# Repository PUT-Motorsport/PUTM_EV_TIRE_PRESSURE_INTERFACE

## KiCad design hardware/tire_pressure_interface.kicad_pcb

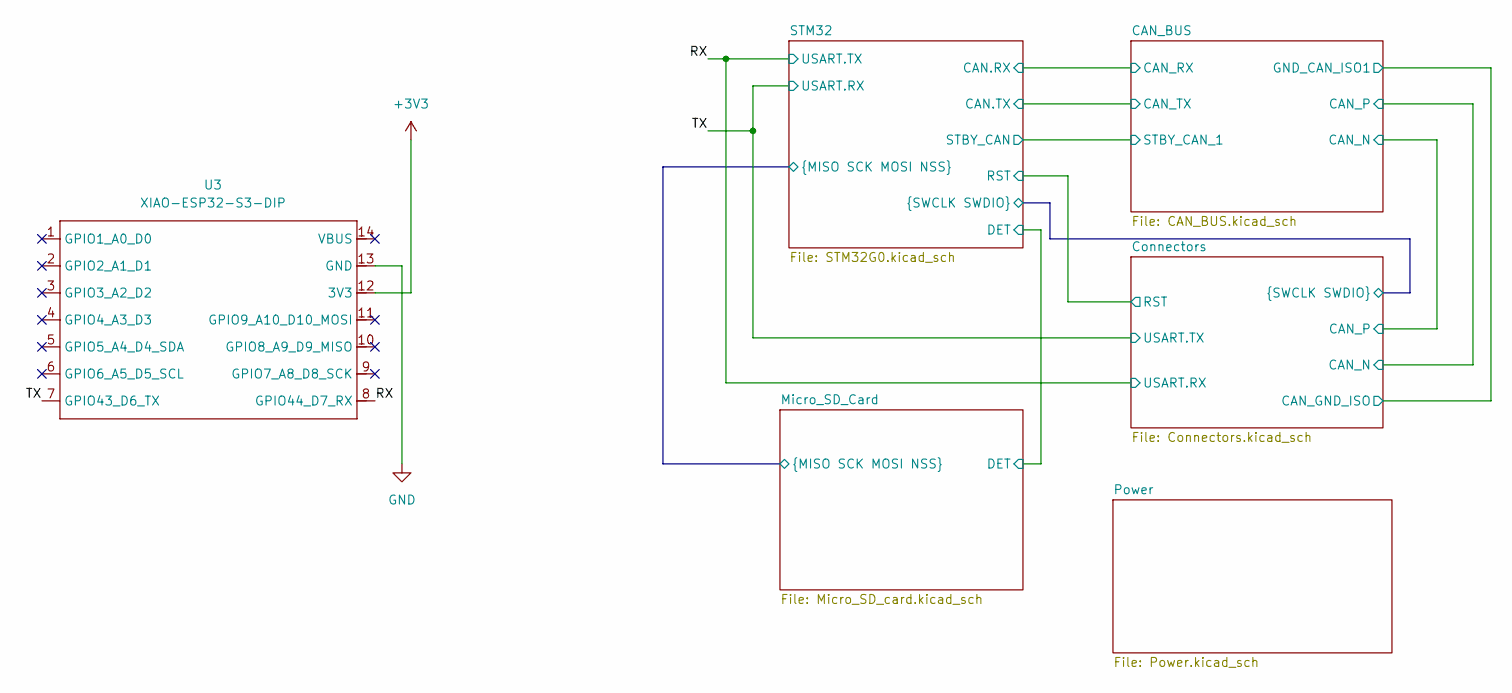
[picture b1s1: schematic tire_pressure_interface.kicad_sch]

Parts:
U3: XIAO-ESP32-S3-DIP

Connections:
+3V3: U3.12 (3V3); also elsewhere on the board
/RX: U3.8 (GPIO44_D7_RX); also elsewhere on the board
/TX: U3.7 (GPIO43_D6_TX); also elsewhere on the board
GND: U3.13 (GND); also elsewhere on the board

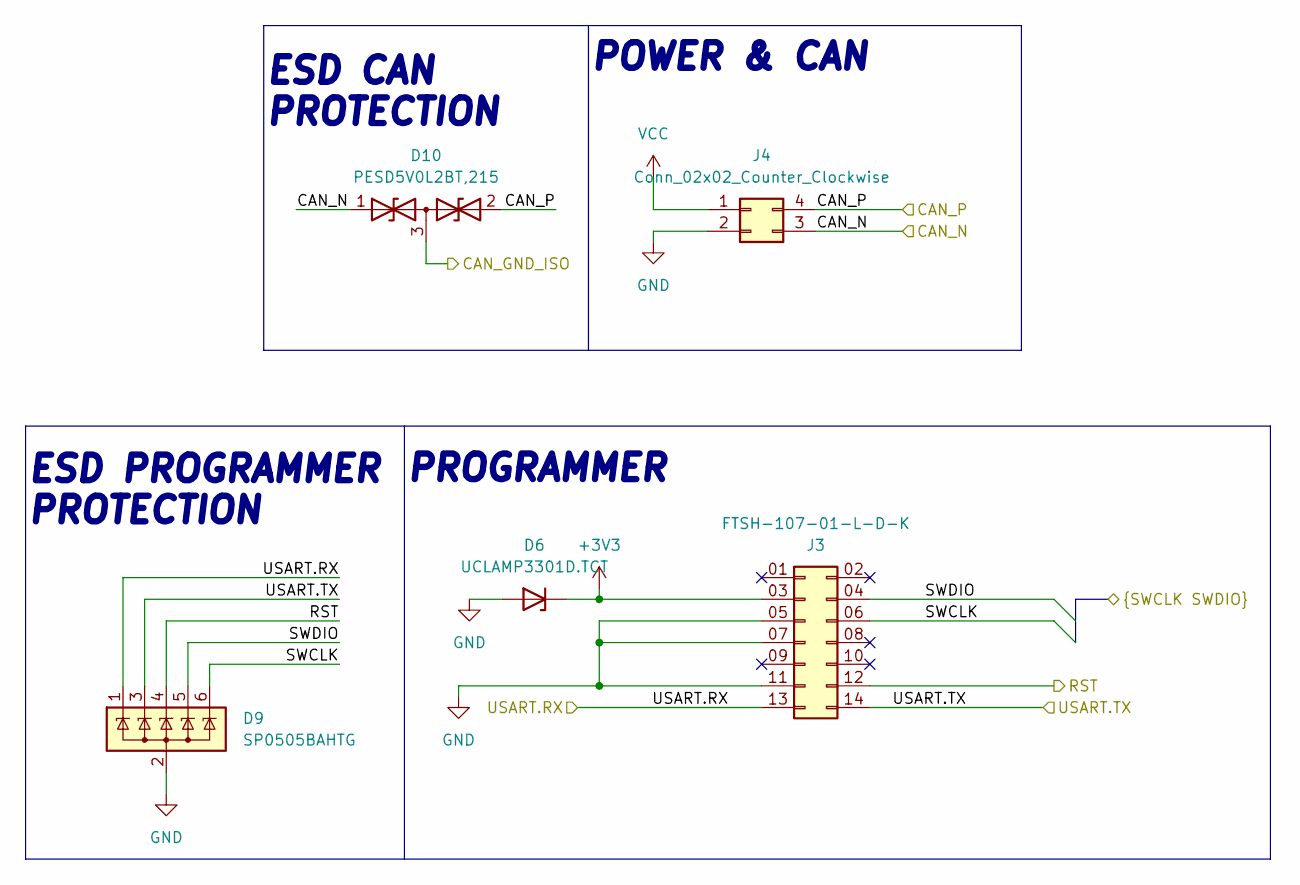
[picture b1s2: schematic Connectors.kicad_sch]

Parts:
D6: UCLAMP3301D.TCT; D_SOD-323_HandSoldering; Mouser number 947-UCLAMP3301D.TCT
D9: SP0505BAHTG; SOT-23-6_Handsoldering; Mouser Part Number 576-SP0505BAHTG
D10: PESD5V0L2BT,215; SOT-23-3; Mouser Part Number 771-PESD5V0S2BT-QR
J3: FTSH-107-01-L-D-K; SAMTEC_FTSH-107-01-L-D-K; Mouser Part Number 200-FTSH10701LDK
J4: Conn_02x02_Counter_Clockwise; JST_EH_S4B-EH_1x04_P2.50mm_Horizontal; Mouser part number 306-S4B-EHLFSN

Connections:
+3V3: D6.1 (K), J3.03 (Pin_3); also elsewhere on the board
/CAN_BUS/GND_CAN_ISO1: D10.3 (common); also elsewhere on the board
/Connectors/CAN_N: D10.1 (A1), J4.3; also elsewhere on the board
/Connectors/CAN_P: D10.2 (A2), J4.4; also elsewhere on the board
/Connectors/RST: D9.4 (K), J3.12; also elsewhere on the board
/Connectors/SWCLK: D9.6 (K), J3.06 (Pin_6); also elsewhere on the board
/Connectors/SWDIO: D9.5 (K), J3.04 (Pin_4); also elsewhere on the board
/RX: D9.1 (K), J3.13; also elsewhere on the board
/TX: D9.3 (K), J3.14; also elsewhere on the board
GND: D6.2 (A), D9.2 (A), J3.05 (Pin_5), J3.07 (Pin_7), J3.11, J4.2; also elsewhere on the board
VCC: J4.1; also elsewhere on the board

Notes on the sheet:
ESD PROGRAMMER PROTECTION
PROGRAMMER
POWER & CAN
ESD CAN PROTECTION

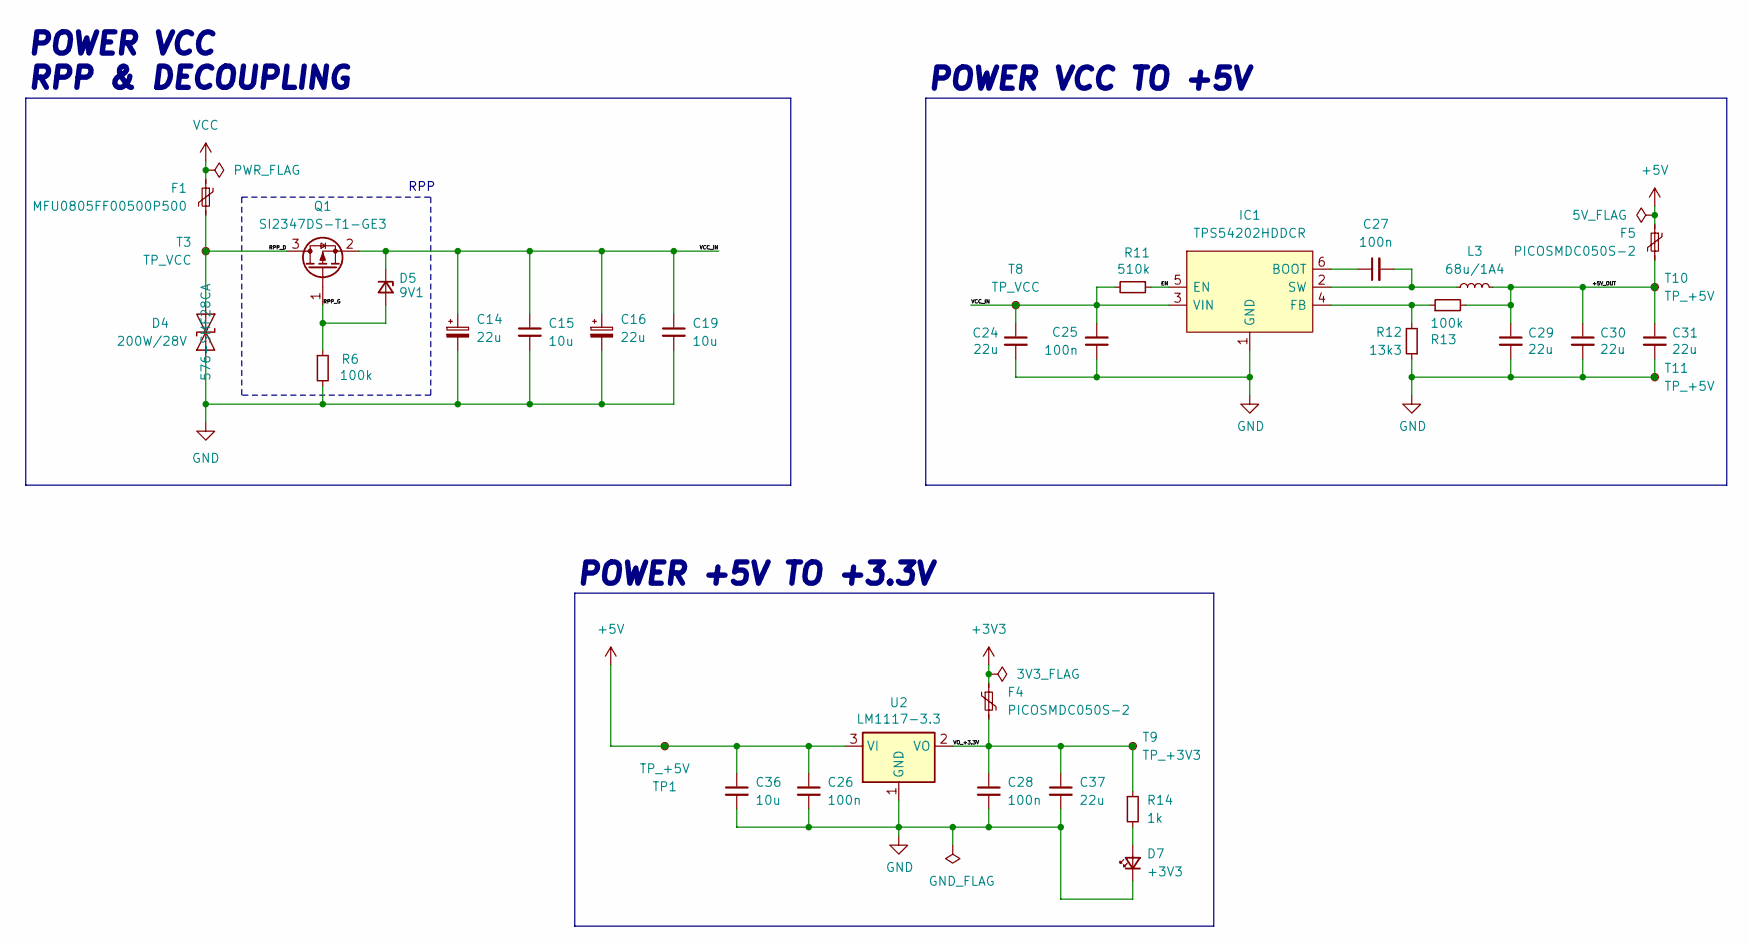
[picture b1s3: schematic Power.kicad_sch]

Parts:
C14, C16: 22u; CP_Elec_4x5.8; Mouser part number 647-UCM1V220MCL1GS
C15, C19: 10u; C_0805_2012Metric_Pad1.18x1.45mm_HandSolder; Mouser part number 810-C2012X5R1V106M0C
C24, C29, C30, C31: 22u; C_0805_2012Metric_Pad1.18x1.45mm_HandSolder; Manufacturer_Part_Number CL21A107MQYNNWE; Mouser Part Number 81-ZRA21CR61E226ME1L
C25, C27: 100n; C_0603_1608Metric_Pad1.08x0.95mm_HandSolder; Manufacturer_Part_Number MAJCU168BB7104KTEA01; Mouser Part Number 963-MAJCU168BB7104KT
C26, C28: 100n; C_0603_1608Metric_Pad1.08x0.95mm_HandSolder; Mouser part number 963-MAJCU168BB7104KT
C36: 10u; C_0603_1608Metric_Pad1.08x0.95mm_HandSolder; Mouser part number 187-CL10A106MA8NRWC
C37: 22u; C_0805_2012Metric_Pad1.18x1.45mm_HandSolder; Mouser part number 81-ZRA21CR61E226ME1L
D4: 200W/28V; D_SOD-123; Mouser part number 576-SMF28CA
D5: 9V1; D_SOD-323_HandSoldering; Mouser part number 863-SZMM3Z9V1T1G
D7: +3V3; LED_0603_1608Metric_Pad1.05x0.95mm_HandSolder
F1: MFU0805FF00500P500; Fuse_0805_2012Metric_Pad1.15x1.40mm_HandSolder; Mouser part number 594-MFU0805FF00500P1
F4, F5: PICOSMDC050S-2; Fuse_0805_2012Metric_Pad1.15x1.40mm_HandSolder
IC1: TPS54202HDDCR; SOT-23-6_Handsoldering; Mouser Part Number 595-TPS54202HDDCR
L3: 68u/1A4; L_TDK_VLS6045EX_VLS6045AF; Mouser Part Number 810-VLS6045EX-680M
Q1: SI2347DS-T1-GE3; SOT-23-3; Mouser part number 78-SI2347DS-T1-GE3
R6: 100k; R_0603_1608Metric_Pad0.98x0.95mm_HandSolder; Mouser part number 660-RK73B1JTTD104J
R11: 510k; R_0603_1608Metric_Pad0.98x0.95mm_HandSolder; Manufacturer_Part_Number RT0603DRD07510KL; Mouser Part Number 603-RT0603DRD07510KL
R12: 13k3; R_0603_1608Metric_Pad0.98x0.95mm_HandSolder; Manufacturer_Part_Number RT0603DRE0713K3L; Mouser Part Number 603-RT0603DRE0713K3L
R13: 100k; R_0603_1608Metric_Pad0.98x0.95mm_HandSolder; Manufacturer_Part_Number RT0603DRE07100KL; Mouser Part Number 603-RT0603DRE07100KL
R14: 1k; R_0603_1608Metric_Pad0.98x0.95mm_HandSolder
T3, T8: TP_VCC; TestPoint_Pad_1.0x1.0mm
T9: TP_+3V3; TestPoint_Pad_1.0x1.0mm
T10, T11: TP_+5V; TestPoint_Pad_1.0x1.0mm
TP1: TP_+5V; TestPoint_Pad_1.0x1.0mm
U2: LM1117-3.3; SOT-223-3_TabPin2

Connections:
+3V3: F4.1; also elsewhere on the board
+5V: C26.1, C36.1, F5.1, TP1.1 (1_1), U2.3 (VI); also elsewhere on the board
/Power/+5V_OUT: C29.1, C30.1, C31.1, F5.2, L3.2, R13.2, T10.1 (1_1)
/Power/EN: IC1.5 (EN), R11.1
/Power/RPP_D: D4.2 (A2), F1.2, Q1.3 (D), T3.1 (1_1)
/Power/RPP_G: D5.2 (A), Q1.1 (G), R6.1
/Power/VCC_IN: C14.1, C15.1, C16.1, C19.1, C24.1, C25.2, D5.1 (K), IC1.3 (VIN), Q1.2 (S), R11.2, T8.1 (1_1)
/Power/VO_+3.3V: C28.1, C37.1, F4.2, R14.1, T9.1 (1_1), U2.2 (VO)
GND: C14.2, C15.2, C16.2, C19.2, C24.2, C25.1, C26.2, C28.2, C29.2, C30.2, C31.2, C36.2, C37.2, D4.1 (A1), D7.1 (K), IC1.1 (GND), R6.2, R12.1, T11.1 (1_1), U2.1 (GND); also elsewhere on the board
unnamed: D7.2 (A), R14.2
unnamed: C27.1, IC1.6 (BOOT)
unnamed: IC1.4 (FB), R12.2, R13.1
unnamed: C27.2, IC1.2 (SW), L3.1
VCC: F1.1; also elsewhere on the board

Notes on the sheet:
POWER VCC TO +5V
POWER +5V TO +3.3V
POWER VCC RPP & DECOUPLING
RPP

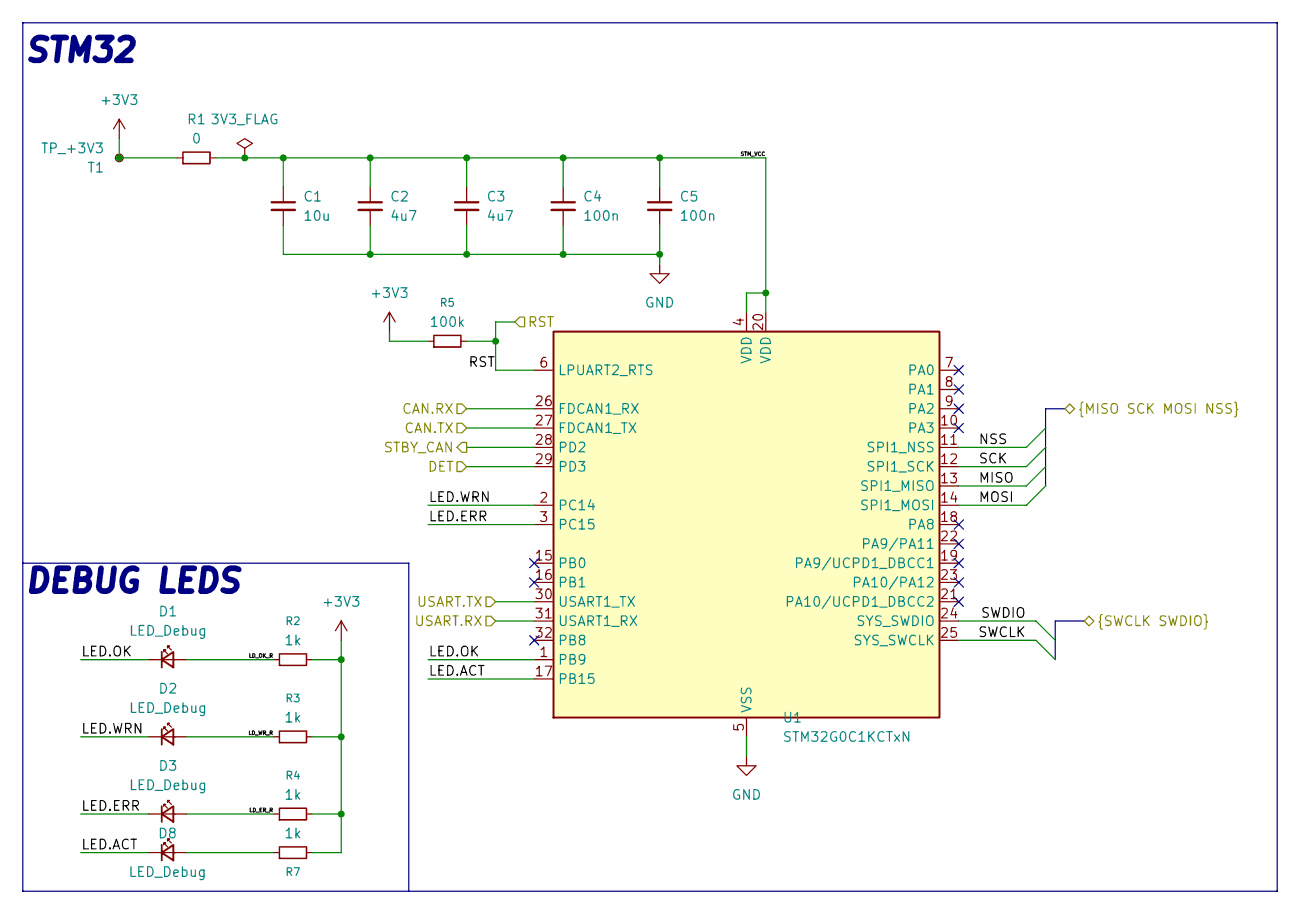
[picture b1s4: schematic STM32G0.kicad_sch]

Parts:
C1: 10u; C_0603_1608Metric_Pad1.08x0.95mm_HandSolder; Mouser Part Number 187-CL10A106MA8NRWC
C2, C3: 4u7; C_0603_1608Metric_Pad1.08x0.95mm_HandSolder; Mouser part number 810-C1608X5R1E475K
C4, C5: 100n; C_0603_1608Metric_Pad1.08x0.95mm_HandSolder; Mouser part number 963-MAJCU168BB7104KT
D1: LED_Debug; LED_0603_1608Metric_Pad1.05x0.95mm_HandSolder; Mouser part number 720-Q65113A7469
D2: LED_Debug; LED_0603_1608Metric_Pad1.05x0.95mm_HandSolder; Mouser part number 720-Q65113A5256
D3: LED_Debug; LED_0603_1608Metric_Pad1.05x0.95mm_HandSolder; Mouser part number 720-Q65113A7466
D8: LED_Debug; LED_0603_1608Metric_Pad1.05x0.95mm_HandSolder; Mouser part number 720-LYQ976.01
R1: 0; R_0603_1608Metric_Pad0.98x0.95mm_HandSolder; Mouser Part Number 71-CRCW06030000Z0ED
R2, R3, R4, R7: 1k; R_0603_1608Metric_Pad0.98x0.95mm_HandSolder; Mouser Part Number 71-CRCW06031K00FKED
R5: 100k; R_0603_1608Metric_Pad0.98x0.95mm_HandSolder; Mouser Part Number 603-RT0603DRE07100KL
T1: TP_+3V3; TestPoint_Pad_1.0x1.0mm
U1: STM32G0C1KCTxN; LQFP-32_7x7mm_P0.8mm; Mouser Part Number 511-STM32G0C1KCT6N

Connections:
+3V3: R1.1, R2.2, R3.2, R4.2, R5.1, R7.2, T1.1 (1_1); also elsewhere on the board
/CAN_BUS/CAN_RX: U1.26 (FDCAN1_RX); also elsewhere on the board
/CAN_BUS/CAN_TX: U1.27 (FDCAN1_TX); also elsewhere on the board
/CAN_BUS/STBY_CAN_1: U1.28 (PD2); also elsewhere on the board
/Connectors/RST: R5.2, U1.6 (LPUART2_RTS); also elsewhere on the board
/Connectors/SWCLK: U1.25 (SYS_SWCLK); also elsewhere on the board
/Connectors/SWDIO: U1.24 (SYS_SWDIO); also elsewhere on the board
/Micro_SD_Card/DET: U1.29 (PD3); also elsewhere on the board
/Micro_SD_Card/MISO: U1.13 (SPI1_MISO); also elsewhere on the board
/Micro_SD_Card/MOSI: U1.14 (SPI1_MOSI); also elsewhere on the board
/Micro_SD_Card/NSS: U1.11 (SPI1_NSS); also elsewhere on the board
/Micro_SD_Card/SCK: U1.12 (SPI1_SCK); also elsewhere on the board
/RX: U1.30 (USART1_TX); also elsewhere on the board
/STM32/LD_ER_R: D3.2 (A), R4.1
/STM32/LD_OK_R: D1.2 (A), R2.1
/STM32/LD_WR_R: D2.2 (A), R3.1
/STM32/LED.ACT: D8.1 (K), U1.17 (PB15)
/STM32/LED.ERR: D3.1 (K), U1.3 (PC15)
/STM32/LED.OK: D1.1 (K), U1.1 (PB9)
/STM32/LED.WRN: D2.1 (K), U1.2 (PC14)
/STM32/STM_VCC: C1.1, C2.1, C3.1, C4.1, C5.1, R1.2, U1.4 (VDD), U1.20 (VDD)
/TX: U1.31 (USART1_RX); also elsewhere on the board
GND: C1.2, C2.2, C3.2, C4.2, C5.2, U1.5 (VSS); also elsewhere on the board
unnamed: D8.2 (A), R7.1

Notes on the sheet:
DEBUG LEDS
STM32

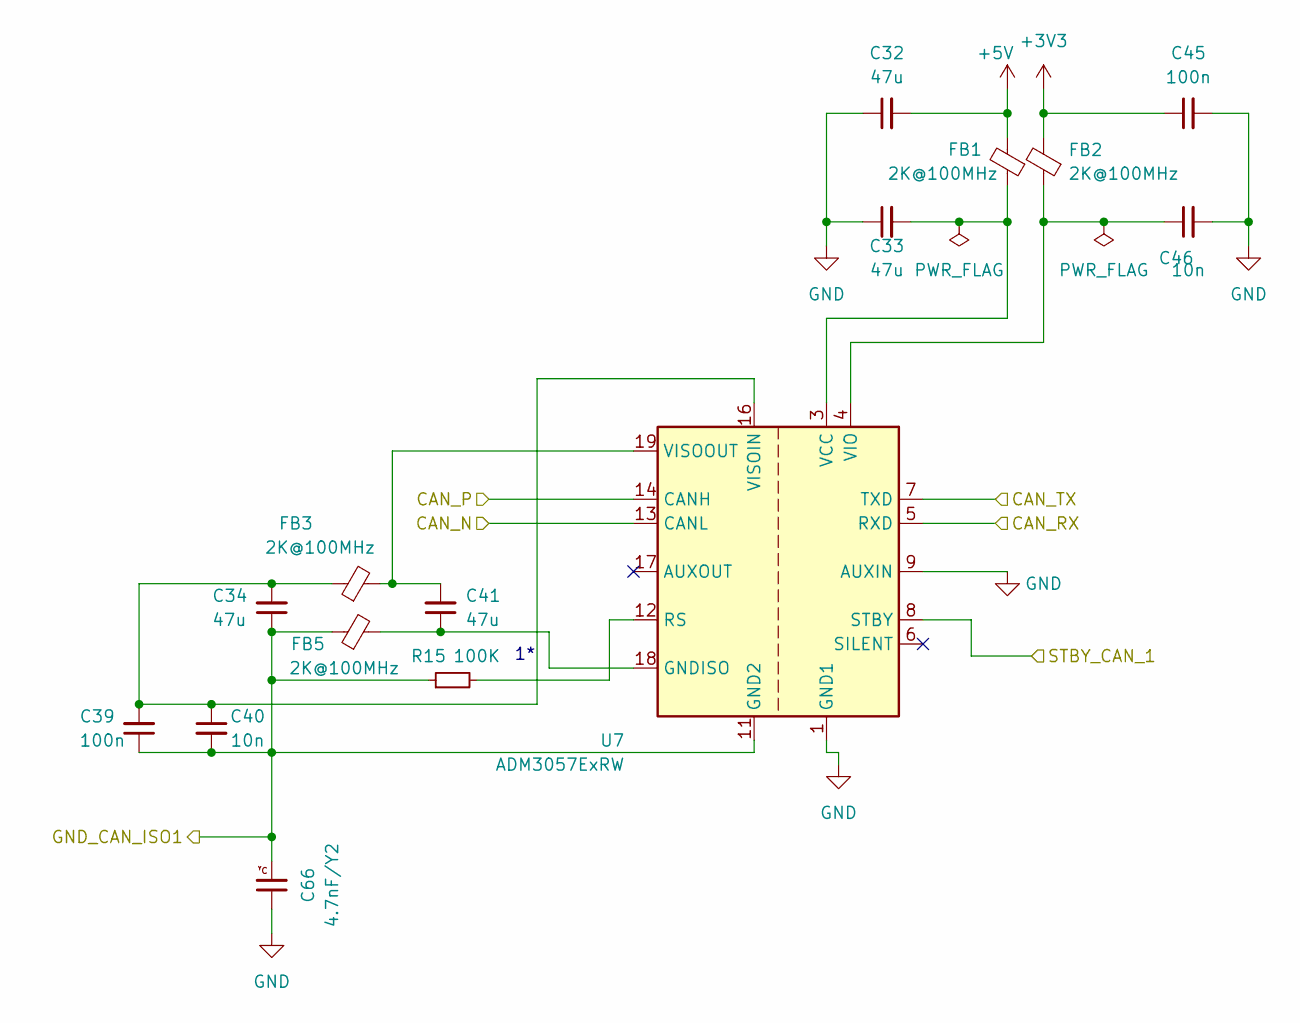
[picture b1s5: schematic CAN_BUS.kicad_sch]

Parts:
C32, C33, C34, C41: 47u; C_0805_2012Metric_Pad1.18x1.45mm_HandSolder; Mouser Part Number 81-GRM21BR60J476M01L
C39, C45: 100n; C_0603_1608Metric_Pad1.08x0.95mm_HandSolder; Mouser Part Number 963-MAJCU168BB7104KT
C40, C46: 10n; C_0603_1608Metric_Pad1.08x0.95mm_HandSolder; Mouser Part Number 81-GCJ188R71E103KA1D
C66: 4.7nF/Y2; CAPC5727X254N; Mouser Part Number 77-HV2225Y472KXVATHV
FB1, FB2, FB3, FB5: 2K@100MHz; L_0805_2012Metric_Pad1.05x1.20mm_HandSolder; Mouser Part Number 623-2508052027Y1
R15: 100K; R_0603_1608Metric_Pad0.98x0.95mm_HandSolder; Mouser Part Number 279-1-72225-5
U7: ADM3057ExRW; SOIC-20W_7.5x12.8mm_P1.27mm; Mouser Part Number 584-ADM3057EBRWZ

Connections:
+3V3: C45.1, FB2.2; also elsewhere on the board
+5V: C32.2, FB1.2; also elsewhere on the board
/CAN_BUS/CAN_RX: U7.5 (RXD); also elsewhere on the board
/CAN_BUS/CAN_TX: U7.7 (TXD); also elsewhere on the board
/CAN_BUS/GND_CAN_ISO1: C34.1, C39.1, C40.2, C66.2, FB5.1, R15.1, U7.11 (GND2), U7.15 (GND2); also elsewhere on the board
/CAN_BUS/STBY_CAN_1: U7.8 (STBY); also elsewhere on the board
/Connectors/CAN_N: U7.14 (CANH); also elsewhere on the board
/Connectors/CAN_P: U7.13 (CANL); also elsewhere on the board
GND: C32.1, C33.1, C45.2, C46.2, C66.1, U7.1 (GND1), U7.2 (GND1), U7.9 (AUXIN), U7.10 (GND1); also elsewhere on the board
unnamed: C41.1, FB5.2, U7.18 (GNDISO), U7.20 (GNDISO)
unnamed: R15.2, U7.12 (RS)
unnamed: C33.2, FB1.1, U7.3 (VCC)
unnamed: C46.1, FB2.1, U7.4 (VIO)
unnamed: C34.2, C39.2, C40.1, FB3.1, U7.16 (VISOIN)
unnamed: C41.2, FB3.2, U7.19 (VISOOUT)

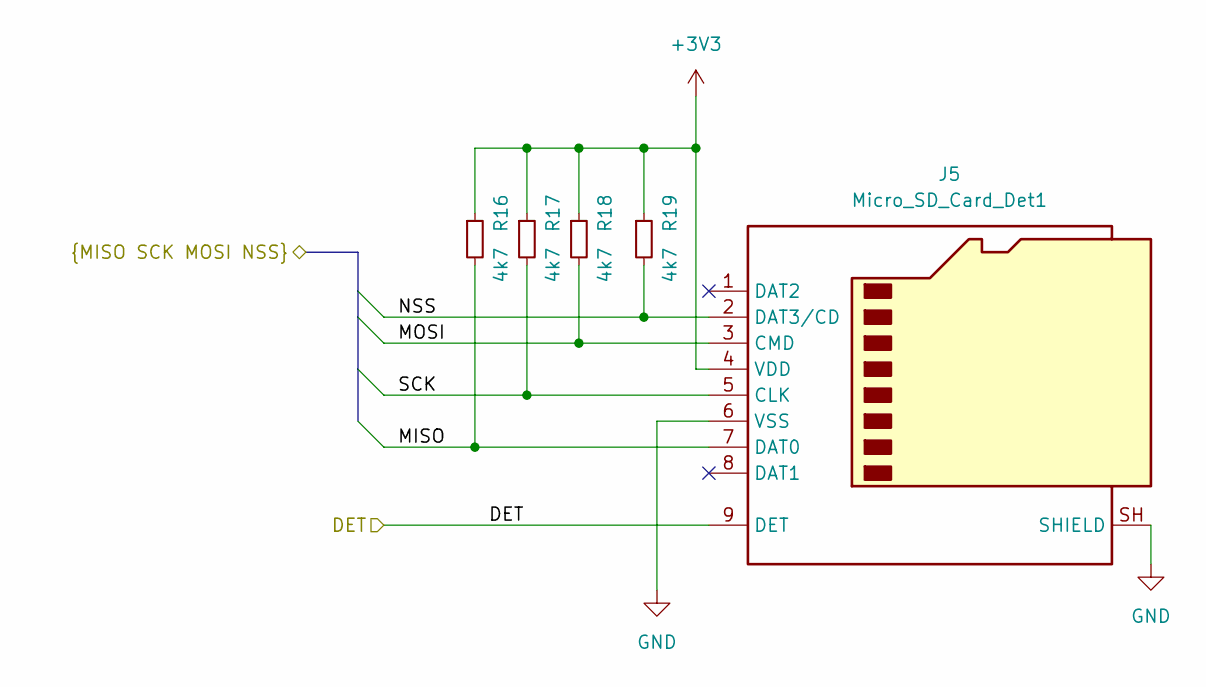
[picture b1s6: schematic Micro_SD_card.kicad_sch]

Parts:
J5: Micro_SD_Card_Det1; microSD_HC_Hirose_DM3AT-SF-PEJM5; Mouser part number 798-DM3AT-SF-PEJM5
R16, R17, R18, R19: 4k7; R_0603_1608Metric_Pad0.98x0.95mm_HandSolder; Mouser Part Number 71-CRCW0603-4.7K-E3

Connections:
+3V3: J5.4 (VDD), R16.1, R17.1, R18.1, R19.1; also elsewhere on the board
/Micro_SD_Card/DET: J5.9 (DET); also elsewhere on the board
/Micro_SD_Card/MISO: J5.7 (DAT0), R16.2; also elsewhere on the board
/Micro_SD_Card/MOSI: J5.3 (CMD), R18.2; also elsewhere on the board
/Micro_SD_Card/NSS: J5.2 (DAT3/CD), R19.2; also elsewhere on the board
/Micro_SD_Card/SCK: J5.5 (CLK), R17.2; also elsewhere on the board
GND: J5.6 (VSS), J5.SH (SHIELD); also elsewhere on the board

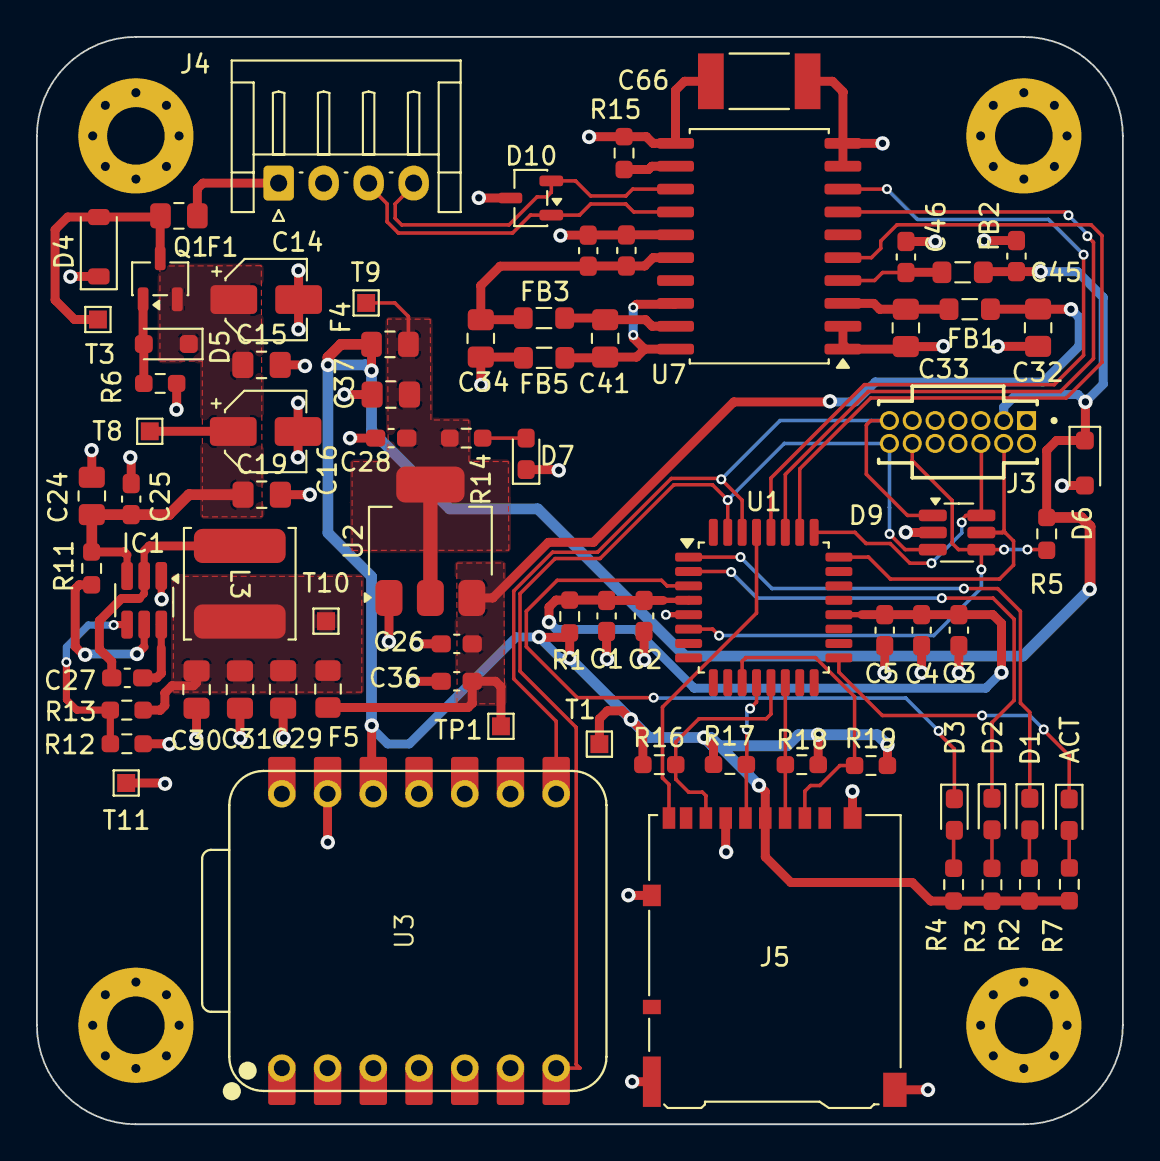
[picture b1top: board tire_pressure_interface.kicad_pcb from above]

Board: 4 copper layers, 60.3 x 60.4 mm, 78 parts (0 on the bottom side), 45 nets.

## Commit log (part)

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2026-04-23 Initial commit: complete schematic
2026-04-24 reorganization of project folders acording to templates
2026-04-25 added missing files
2026-04-25 reorganize SPI signals into bus
2026-05-01 initial component placement
2026-05-03 pcb routing
2026-05-12 power section routing
2026-05-25 power section and isocan layout
2026-06-04 STM32G0 and micro sd layout
2026-06-09 routing and PCB outline
2026-06-16 changed layout
2026-06-16 fixed drc issues
2026-06-22 changed pcb layout
2026-06-25 fixed routing issues
2026-06-25 added missing TVS diode
2026-06-25 added led description
2026-06-25 removed 3v3 bcu fill
2026-06-26 improved 3V3 routing
2026-06-30 fixed 3v3 routing
